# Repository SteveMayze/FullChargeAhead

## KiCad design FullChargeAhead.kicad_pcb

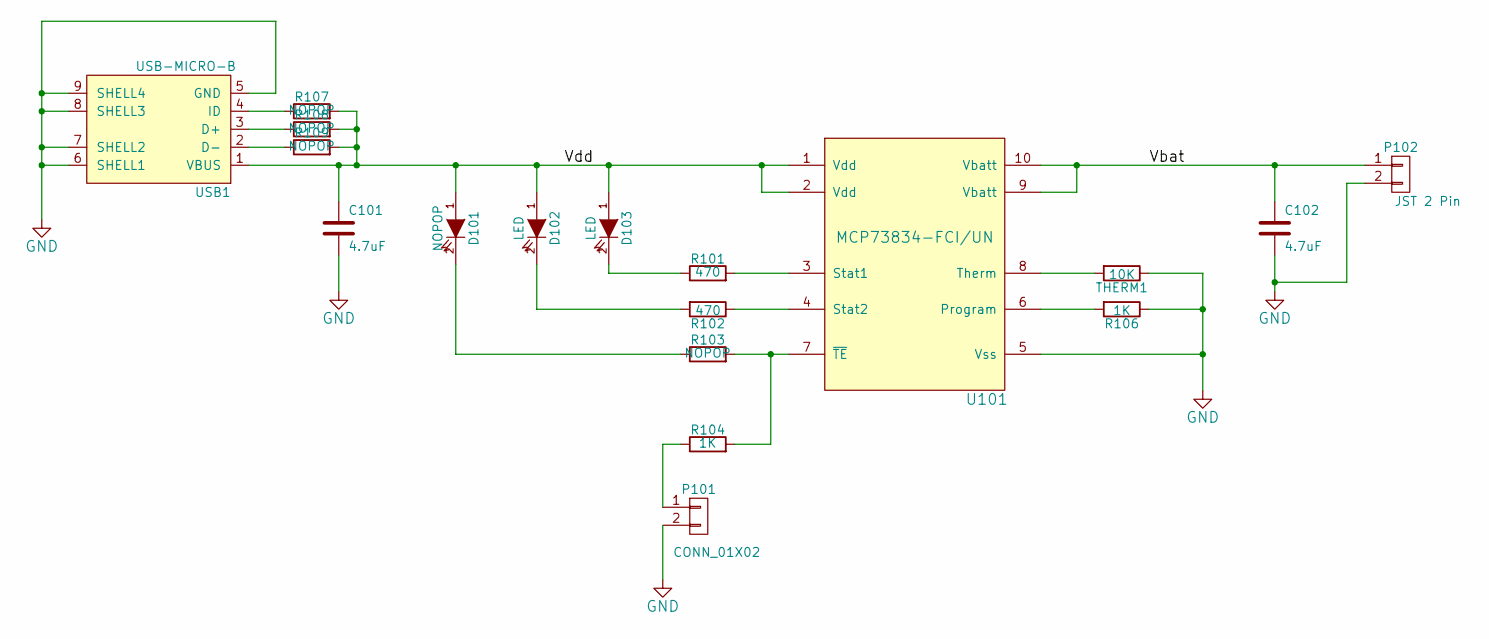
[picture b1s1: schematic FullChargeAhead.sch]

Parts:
C101, C102: 4.7uF; C_1206_HandSoldering; MPN Value
D101: NOPOP; LED-0805; MPN N/A
D102, D103: LED; LED-0805; MPN KP-2012EC
P101: CONN_01X02; Pin_Header_Straight_1x02
P102: JST 2 Pin; JST_2Pin; MPN S2B-PH-K-S
R101, R102: 470; R_0805_HandSoldering
R103, R107, R108, R109: NOPOP; R_0805_HandSoldering
R104, R106: 1K; R_0805_HandSoldering
THERM1: 10K; R_0805_HandSoldering
U101: MCP73834-FCI/UN; MSOP-10_3x3mm_Pitch0.5mm; MPN MCP73834-FCI/UN
USB1: USB-MICRO-B; USB_Micro_B; MPN 10118193-0001LF

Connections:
/Vbat: C102.1, P102.1, U101.9 (Vbatt), U101.10 (Vbatt)
/Vdd: C101.1, D101.1 (A), D102.1 (A), D103.1 (A), R107.2, R108.2, R109.2, U101.1 (Vdd), U101.2 (Vdd), USB1.1 (VBUS)
GND: C101.2, C102.2, P101.2, P102.2, R106.1, THERM1.1, U101.5 (Vss), USB1.5 (GND), USB1.6 (SHELL1), USB1.7 (SHELL2), USB1.8 (SHELL3), USB1.9 (SHELL4)
unnamed: D101.2 (K), R103.1
unnamed: D102.2 (K), R102.2
unnamed: D103.2 (K), R101.1
unnamed: P101.1, R104.1
unnamed: R101.2, U101.3 (Stat1)
unnamed: R102.1, U101.4 (Stat2)
unnamed: R103.2, R104.2, U101.7 (~TE)
unnamed: R106.2, U101.6 (Program)
unnamed: R107.1, USB1.4 (ID)
unnamed: R108.1, USB1.3 (D+)
unnamed: R109.1, USB1.2 (D-)
unnamed: THERM1.2, U101.8 (Therm)

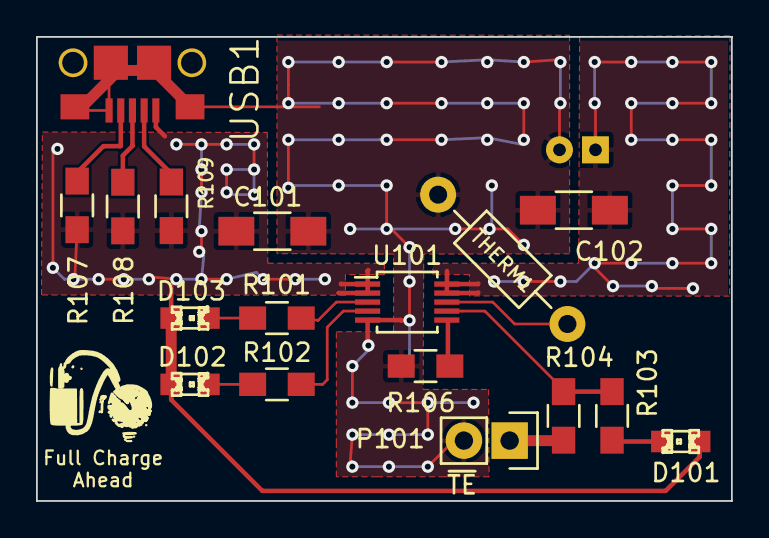
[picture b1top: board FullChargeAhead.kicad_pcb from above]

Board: 2 copper layers, 38.6 x 25.8 mm, 18 parts (1 on the bottom side), 15 nets.

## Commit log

2015-03-10 Created the inital checkin for the FullChargeAheard Module for RWI
2015-03-21 Initial checkin of the schematic
2015-03-23 Added the new library, created the micro usb foot print and started the layout
2015-03-27 Model update after component resze
2015-03-28 Preperation for layout
2015-03-28 Corrected the footprint for the JST connector
2015-03-29 Front Cu Layout done
2015-03-29 Back Cu Layout and changes to front Cu. Also edge cuts added
2015-03-29 Back Cu Layout and changes to front Cu. Also edge cuts added #2
2015-03-29 Base vias for stitching added
2015-03-29 Via stitched
2015-03-29 Completed layout and archive for Oshpark
2015-03-30 Final layout and oshpark review
2015-03-30 Added .DS_Store to the gitignore for MacOSX
2015-03-30 The last final layout and shpark review
2015-03-31 Started BOM
2015-03-31 More on the BOM
2015-03-31 BOM and script
2015-05-16 Some changes and test results
2015-11-22 Updated the documentation
